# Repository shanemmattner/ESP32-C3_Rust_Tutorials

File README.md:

# ESP32-C3 Rust Tutorials

Various `embedded Rust tutorials` using the [ESP32-C3](https://www.espressif.com/en/products/socs/esp32-c3). We'll work towards making a `remote data logger` by first implementing peripherals we will need to build the larger project.

Each tutorial below has a `YouTube video` link where I will start with a blank project and implement a peripherals using the latest [esp-idf-hal](https://github.com/esp-rs/esp-idf-hal) version. 

## Repo organization

- [Tutorials](https://github.com/shanemmattner/ESP32-C3_Rust_Tutorials/tree/main/Tutorials): Source code for the [YouTube tutorials](https://youtube.com/playlist?list=PLkch9g9DEE0Lkm1LqcD7pZNDmXEczOo-a)
- [WIP](https://github.com/shanemmattner/ESP32-C3_Rust_Tutorials/tree/main/WIP): Half-baked crates that may have some useful code in the future
- [docs](https://github.com/shanemmattner/ESP32-C3_Rust_Tutorials/tree/main/docs): Various datasheets, books, and technical manuals
- [submodules](https://github.com/shanemmattner/ESP32-C3_Rust_Tutorials/tree/main/docs): All of the submodules for this repository.
   - <b>[referecnce projects](https://github.com/shanemmattner/ESP32-C3_Rust_Tutorials/tree/main/submodules/reference_projects)</b>: A huge collection of embedded Rust projects that I copy code from
- [Data-Logger-PCB](https://github.com/shanemmattner/ESP32-C3_Rust_Tutorials/tree/main/Data-Logger-PCB): KiCAD hardware designs for ESP32-C3 data logger PCB

## Part 0: Remote Data Logger MVP
[Minimum viable product](https://en.wikipedia.org/wiki/Minimum_viable_product) project where we'll implement all the peripherals and features we need for the data logger
- 4 ADC's
- 16 Digital I/O
- DHT11
- SD card logging
- UART CLI Shell

### Peripheral Tutorials
- [p0-output](https://youtu.be/vUSHaogHs1s): Make the "Hellow World" of embedded systems: a `Blinky application` to periodically turn an LED on and off
- [p1-input](https://youtu.be/2IY27b9TT2k): Add a button to turn the blinking logic on and off
- [p2-threads](https://youtu.be/ht5t39dEa4E): Move the button logic and LED logic to their own thread and pass messages between threads with [crossbeams channel](https://docs.rs/crossbeam/latest/crossbeam/channel/index.html)
- [p3-adc](https://youtu.be/07SVj6R_AhA): Read an [analog-to-digital converter channel](https://en.wikipedia.org/wiki/Analog-to-digital_converter) and print out the value
- [p4-dht11](tbd): Read a [DHT11](https://www.mouser.com/datasheet/2/758/DHT11-Technical-Data-Sheet-Translated-Version-1143054.pdf) for temperature and humidity data  
- [p5-i2c](https://youtu.be/NvEnHJPpavo): Configure and use a [SX1509 GPIO Expander](https://www.sparkfun.com/products/13601) through [I2C](https://learn.sparkfun.com/tutorials/i2c)
- [p6-spi](https://youtu.be/PUL8ehH6eUg): Write a string to a uSD card over SPI using [embedded-sdmmc](https://github.com/rust-embedded-community/embedded-sdmmc-rs) crate
- [p7-uart](https://youtu.be/-xEivxWe29M): Receiver characters from the UART and send them back when we detect a [carriage return](https://developer.mozilla.org/en-US/docs/Glossary/CRLF)

### Application Tutorials
- [p8-cli-shell](): Create a simple [CLI shell](https://interrupt.memfault.com/blog/firmware-shell) to interact with the ESP32-C3 over UART 
- [p9-adc-stream](): Configure ADC's to continuously read and make that data available to other parts of the application through a mutex
- [p10-log-values](): Log all the values read from the ADC's
- [p11-digital-stream](): Continuously read the SX1509 inputs and log to SD card

## Part 1: 
For the next part of the project we will add in features listed below:
- Debugging
- Logging
- FSM/HSM
- Wifi
- MQTT
- OTA
- Pub/sub
- Crash dumps & diagnostics

Other features I'd like to add but don't have a clear example for yet:
- DMA
- Timer usage

<details>
  <summary>Development environment setup</summary>
  
1. [Install Rust](https://esp-rs.github.io/book/installation/installation.html) and associated build tools
2. Start a project using the [esp-idf-template](https://github.com/esp-rs/esp-idf-template) from the private repo home `dir`. I chose all the default options
```
# STD Project
cargo generate https://github.com/esp-rs/esp-idf-template cargo
# NO-STD (Bare-metal) Project
cargo generate https://github.com/esp-rs/esp-template
```
3. Build the `Hello World` program by running `cargo build` in the new project dir. This will take a while to build the first time:
```
cd esp32-rust
cargo build
...
Finished dev [optimized + debuginfo] target(s) in 6m 40s
```
4. Flash the ESP32 with the build artifact:
```
espflash /dev/ttyACM0 target/riscv32imc-esp-espidf/debug/project
```
5. Connect to ESP32 and monitor
```
espmonitor /dev/ttyACM0
```
 </details>

<details>
  <summary>Misc</summary>
  
[Singletons in Embedded Rust](https://docs.rust-embedded.org/book/peripherals/singletons.html)

Pull in code for submodules with:
```
git submodule update --init --recursive
```
</details>

<details>
  <summary>Links</summary>

- [150+ ESP32 project](https://microcontrollerslab.com/esp32-tutorials-projects/)
- [Wokwi ESP32 Rust](https://wokwi.com/rust)
- [ESP32 Tutorials](https://embeddedexplorer.com/esp32/)
- [160+ ESP32 Projects, Tutorials, and Guides](https://randomnerdtutorials.com/projects-esp32/)

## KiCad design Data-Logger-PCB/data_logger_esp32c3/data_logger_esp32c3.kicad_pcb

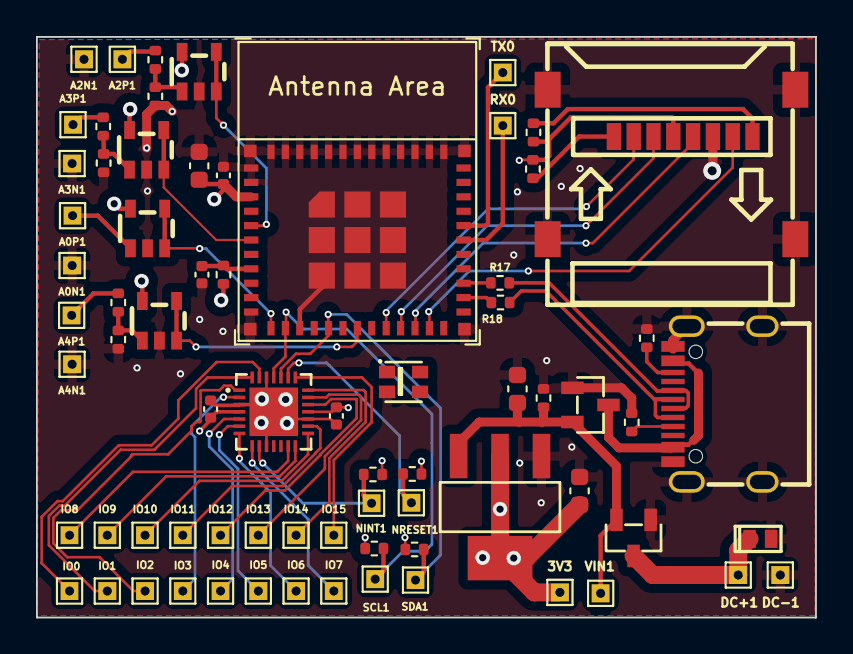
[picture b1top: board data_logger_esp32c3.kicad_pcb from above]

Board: 4 copper layers, 43.3 x 32.3 mm, 72 parts (0 on the bottom side), 47 nets.

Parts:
3V3: TestPoint; TestPoint_THTPad_1.0x1.0mm_Drill0.5mm
A0N1, A0P1, A2N1, A2P1, A3N1, A3P1, A4N1, A4P1: TestPoint; TestPoint_THTPad_1.0x1.0mm_Drill0.5mm
C1: 1uF; C_0402_1005Metric
C2, C4, C5: 10uF; C_0603_1608Metric
C3, C6, C7: 0.1uF; C_0402_1005Metric
D1: LTVS16H5.0T5G; DFN1610
DC+1: TestPoint; TestPoint_THTPad_1.0x1.0mm_Drill0.5mm
DC-1: TestPoint; TestPoint_THTPad_1.0x1.0mm_Drill0.5mm
IO0, IO1, IO2, IO3, IO4, IO5, IO6, IO7, IO8, IO9, IO10, IO11, IO12, IO13, IO14, IO15: TestPoint; TestPoint_THTPad_1.0x1.0mm_Drill0.5mm
NINT1: TestPoint; TestPoint_THTPad_1.0x1.0mm_Drill0.5mm
NRESET1: TestPoint; TestPoint_THTPad_1.0x1.0mm_Drill0.5mm
R1, R3, R4, R9, R14, R15: 10k; R_0402_1005Metric
R2, R7: 5.1k; R_0402_1005Metric
R5, R6, R13: 1k; R_0402_1005Metric
R8, R16: 4.7k; R_0402_1005Metric
R10: 1.6k; R_0402_1005Metric
R11: 3.92k; R_0402_1005Metric
R12: 7.5k; R_0402_1005Metric
R17, R18: 30.1; R_0402_1005Metric
RX0: TestPoint; TestPoint_THTPad_1.0x1.0mm_Drill0.5mm
SCL1: TestPoint; TestPoint_THTPad_1.0x1.0mm_Drill0.5mm
SD1: 472192001
SDA1: TestPoint; TestPoint_THTPad_1.0x1.0mm_Drill0.5mm
TX0: TestPoint; TestPoint_THTPad_1.0x1.0mm_Drill0.5mm
U1: ESP32-C3-MINI-1
U2: AZ1117IH-3.3TRG1; SOT-223-4
U3: WS2812B-2020
U4, U5, U6, U7: LM321MF
U9, U10: A03401A; SOT-23
U11: SX1509BIULTRT; QFN-28-EP(4x4)
USB-C1: USB-TYPE-C-018
VIN1: TestPoint; TestPoint_THTPad_1.0x1.0mm_Drill0.5mm

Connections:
+3V3: 3V3.1, C2.1, C3.1, C5.1, C6.1, C7.1, R1.2, R3.2, R4.1, R8.2, R14.2, R15.2, R16.2, SD1.4 (VDD), U1.3 (3V3), U2.2 (OUTPUT), U2.4 (VOUT), U3.4 (VDD), U4.5 (V+), U5.5 (V+), U6.5 (V+), U7.5 (V+), U11.4 (VCC1), U11.18 (VCC2)
+5V: U10.3 (D), USB-C1.A4 (VBUS), USB-C1.A9 (VBUS), USB-C1.B4 (VBUS), USB-C1.B9 (VBUS)
ADC1_CH0: U1.12 (GPIO0/ADC1_CH0/XTAL_32K_P), U4.3 (-), U4.4
ADC1_CH2: U1.5 (GPIO2/ADC1_CH2), U5.3 (-), U5.4
ADC1_CH3: U1.6 (GPIO3/ADC1_CH3), U6.3 (-), U6.4
ADC1_CH4: U1.18 (GPIO4/ADC1_CH4), U7.3 (-), U7.4
CS: SD1.2 (DAT3/CD), U1.20 (GPIO6)
D+: R17.1, U1.27 (GPIO19/USB_D+)
D-: R18.1, U1.26 (GPIO18/USB_D-)
DI: SD1.3 (CMD), U1.21 (GPIO7)
DO: SD1.7 (DAT0), U1.23 (GPIO9)
D_CONN+: R17.2, USB-C1.A6 (DP1), USB-C1.B6 (DP2)
D_CONN-: R18.2, USB-C1.A7 (DN1), USB-C1.B7 (DN2)
GND: A0N1.1, A2N1.1, A3N1.1, A4N1.1, C1.2, C2.2, C3.2, C4.2, C5.2, C6.2, C7.2, D1.2 (A), DC-1.1, R2.1, R5.2, R6.2, R7.1, R9.1, R13.2, SD1.6 (VSS), SD1.9 (SHIELD), SD1.10 (SHIELD), SD1.11 (SHIELD), SD1.12 (SHIELD), U1.1 (GND), U1.2 (GND), U1.11, U1.14, U1.36 (GND), U1.37 (GND), U1.38 (GND), U1.39 (GND), U1.40 (GND), U1.41 (GND), U1.42 (GND), U1.43 (GND), U1.44 (GND), U1.45 (GND), U1.46 (GND), U1.47 (GND), U1.48 (GND), U1.49 (GND), U1.50 (GND), U1.51 (GND), U1.52 (GND), U1.53 (GND), U2.1 (ADJ/GND), U3.2 (GND), U4.2 (V-), U5.2 (V-), U6.2 (V-), U7.2 (V-), U9.1 (G), U10.1 (G), U11.3 (GND), U11.10 (ADDR1), U11.17 (GND), U11.26 (ADDR0), U11.29 (PAD), USB-C1.0 (SH), USB-C1.1 (SH), USB-C1.2 (SH), USB-C1.3 (SH), USB-C1.A1 (GND), USB-C1.A12 (GND), USB-C1.B1 (GND), USB-C1.B12 (GND)
I2C_SCL: R8.1, SCL1.1, U1.13 (GPIO1/ADC1_CH1/XTAL_32K_N), U11.25 (SCL)
I2C_SDA: R16.1, SDA1.1, U1.16 (GPIO10), U11.24 (SDA)
NINT: NINT1.1, R15.1, U11.9 (NINT)
NRESET: NRESET1.1, R14.1, U11.23 (NRESET)
unnamed: A2P1.1, R10.1
unnamed: A3P1.1, R11.1
unnamed: A4P1.1, R12.1
unnamed: D1.1 (K), DC+1.1, U9.3 (D)
unnamed: R3.1, SD1.8 (DAT1)
unnamed: R1.1, SD1.1 (DAT2)
unnamed: C1.1, R4.2
unnamed: A0P1.1, U4.1 (+)
unnamed: R10.2, R13.1, U5.1 (+)
unnamed: R5.1, R11.2, U6.1 (+)
unnamed: R6.1, R12.2, U7.1 (+)
unnamed: C4.1, R9.2, U2.3 (INPUT), U9.2 (S), U10.2 (S), VIN1.1
unnamed: IO0.1, U11.27 (IO0)
unnamed: IO1.1, U11.28 (IO1)
unnamed: IO2.1, U11.1 (IO2)
unnamed: IO3.1, U11.2 (IO3)
unnamed: IO4.1, U11.5 (IO4)
unnamed: IO5.1, U11.6 (IO5)
unnamed: IO6.1, U11.7 (IO6)
unnamed: IO7.1, U11.8 (IO7)
unnamed: IO8.1, U11.13 (IO8)
unnamed: IO9.1, U11.14 (IO9)
unnamed: IO10.1, U11.15 (IO10)
unnamed: IO11.1, U11.16 (IO11)
unnamed: IO12.1, U11.19 (IO12)
unnamed: IO13.1, U11.20 (IO13)
unnamed: IO14.1, U11.21 (IO14)
unnamed: IO15.1, U11.22 (IO15)
SCLK: SD1.5 (CLK), U1.22 (GPIO8)

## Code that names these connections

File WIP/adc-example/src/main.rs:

use embedded_hal::adc::OneShot;
use esp_idf_hal::{
    adc::{self, Atten11dB, PoweredAdc},
    gpio,
    prelude::*,
};
use esp_idf_sys as _; // If using the `binstart` feature of `esp-idf-sys`, always keep this module imported
use std::{thread, time::Duration};
static BLINKY_STACK_SIZE: usize = 5000;

fn main() {
    // It is necessary to call this function once. Otherwise some patches to the runtime
    // implemented by esp-idf-sys might not link properly. See https://github.com/esp-rs/esp-idf-template/issues/71
    esp_idf_sys::link_patches();

    let peripherals = Peripherals::take().unwrap();

    let config = adc::config::Config::new().calibration(true);

    // let mut adc1_ch0 = peripherals.pins.gpio0.into_analog_atten_11db().unwrap();
    // let mut adc1_ch1 = peripherals.pins.gpio1.into_analog_atten_11db().unwrap();
    // let mut adc1_ch2 = peripherals.pins.gpio2.into_analog_atten_11db().unwrap();
    // let mut adc1_ch3 = peripherals.pins.gpio3.into_analog_atten_11db().unwrap();
    // let mut adc1_ch4 = peripherals.pins.gpio4.into_analog_atten_11db().unwrap();
    let mut adc2_ch0 = peripherals.pins.gpio5.into_analog_atten_11db().unwrap();

    // let mut adc1 = PoweredAdc::new(peripherals.adc1, config).unwrap();
    let mut adc2 = PoweredAdc::new(peripherals.adc2, config).unwrap();

    let _adc_thread = std::thread::Builder::new()
        .stack_size(BLINKY_STACK_SIZE)
        .spawn(move || loop {
            // let mut adc_reading = adc1.read(&mut adc1_ch0).unwrap();
            // println!("ADC1_0: {}", adc_reading);
            // adc_reading = adc1.read(&mut adc1_ch1).unwrap();
            // println!("ADC1_1: {}", adc_reading);
            // adc_reading = adc1.read(&mut adc1_ch2).unwrap();
            // println!("ADC1_2: {}", adc_reading);
            // adc_reading = adc1.read(&mut adc1_ch3).unwrap();
            // println!("ADC1_3: {}", adc_reading);
            // adc_reading = adc1.read(&mut adc1_ch4).unwrap();
            // println!("ADC1_4: {}", adc_reading);
            let mut adc_reading = adc2.read(&mut adc2_ch0).unwrap();
            println!("ADC2_0: {}", adc_reading);

            thread::sleep(Duration::from_millis(100));
        })
        .unwrap();
}

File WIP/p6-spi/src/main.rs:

use embedded_sdmmc::*;
use esp_idf_hal::{
    adc::{self, *},
    delay::FreeRtos,
    gpio::*,
    peripherals::Peripherals,
    prelude::*,
    spi::config::Duplex,
    spi::*,
};
use esp_idf_sys as _; // If using the `binstart` feature of `esp-idf-sys`, always keep this module imported
use esp_println::println;
use std::time::*;

const FILE_TO_CREATE: &'static str = "logs.txt";

pub struct SdMmcClock;

impl TimeSource for SdMmcClock {
    fn get_timestamp(&self) -> Timestamp {
        Timestamp {
            year_since_1970: 0,
            zero_indexed_month: 0,
            zero_indexed_day: 0,
            hours: 0,
            minutes: 0,
            seconds: 0,
        }
    }
}

fn main() {
    // It is necessary to call this function once. Otherwise some patches to the runtime
    // implemented by esp-idf-sys might not link properly. See https://github.com/esp-rs/esp-idf-template/issues/71
    esp_idf_sys::link_patches();

    println!("Starting 6-spi\nThis application writes ADC readings to a micro-SD card\n");

    let peripherals = Peripherals::take().unwrap();

    // ADC init
    let mut adc1 = AdcDriver::new(
        peripherals.adc1,
        &adc::config::Config::new().calibration(true),
    )
    .unwrap();
    let mut a1_ch0 =
        adc::AdcChannelDriver::<_, adc::Atten11dB<adc::ADC1>>::new(peripherals.pins.gpio0).unwrap();

    // SPI sd card init
    let driver = SpiDriver::new(
        peripherals.spi2,
        peripherals.pins.gpio8,       // SCK
        peripherals.pins.gpio7,       // PICO
        Some(peripherals.pins.gpio9), // POCI
        Dma::Disabled,
    )
    .unwrap();

    let mut spi_config = SpiConfig::new();
    spi_config.duplex = Duplex::Full;
    let _ = spi_config.baudrate(24.MHz().into());
    let spi = SpiDeviceDriver::new(driver, Option::<Gpio6>::None, &spi_config).unwrap();
    let sdmmc_cs = PinDriver::output(peripherals.pins.gpio6).unwrap();
    let mut sdmmc_spi = embedded_sdmmc::SdMmcSpi::new(spi, sdmmc_cs);

    // keep track of the time for logging
    let start_time = Instant::now();

    loop {
        match adc1.read(&mut a1_ch0) {
            Ok(adc_reading) => {
                match sdmmc_spi.acquire() {
                    Ok(block) => {
                        let mut controller = embedded_sdmmc::Controller::new(block, SdMmcClock);

                        let mut volume =
                            controller.get_volume(embedded_sdmmc::VolumeIdx(0)).unwrap();

                        let root_dir = controller.open_root_dir(&volume).unwrap();

                        let mut f = controller
                            .open_file_in_dir(
                                &mut volume,
                                &root_dir,
                                FILE_TO_CREATE,
                                Mode::ReadWriteCreateOrAppend,
                            )
                            .unwrap();

                        f.seek_from_end(0).unwrap();
                        // Create log string
                        let mut log_string: String = start_time.elapsed().as_millis().to_string();
                        log_string.push_str(&",A1_CH0,".to_string());
                        log_string.push_str(&(adc_reading as u32).to_string());
                        log_string.push('\n');
                        // Write the string to the SD card
                        let _bytes_written = controller
                            .write(&mut volume, &mut f, &log_string.as_bytes()[..])
                            .unwrap();
                        println!("String written: {log_string}");

                        controller.close_file(&volume, f).unwrap();
                    }
                    Err(e) => println!("Error acquire SPI bus {:?}", e),
                };
            }
            Err(e) => println!("err reading A1_CH0: {e}\n"),
        }

        FreeRtos::delay_ms(500);
    }
}

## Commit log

2023-01-14 working first blinky
2023-01-16 Added outline to README
2023-01-16 Added thread blinky
2023-01-16 add fsm blinky
2023-01-18 add wifi project
2023-01-18 working blinky with wifi
2023-01-19 wifi test
2023-01-19 added project
2023-01-24 improve blinky thread
2023-01-24 improved ch03 fsm
2023-01-24 improve wifi example
2023-01-24 moved fsm to its own file
2023-01-24 adding more chapters
2023-01-24 edit readme
2023-01-25 add heirarchical state machine example
2023-01-25 adding multi-state machine example
2023-01-26 add submodules
2023-01-26 Rearrange chapters
2023-01-26 Added multi-thread example
2023-01-26 refactor logic
2023-01-26 refactor blinky
2023-01-27 add example with crossbeam
2023-01-29 added no-std example
2023-02-01 adding async example and adc
2023-02-11 update crate versions"
2023-02-11 upgrade crates to latest
2023-02-11 deleted unused project
2023-02-11 modifying submodule
2023-02-11 adding more projects to submodules
2023-02-11 adding reference examples
2023-02-11 more submodules
2023-02-11 remove commented out code
2023-02-11 non-macro working
2023-02-11 updated fsm example to latest esp-idf drivers
2023-02-11 add readme, change name
2023-02-11 hsm working without blinking led
2023-02-11 working hsm with latest esp-idf libraries
2023-02-11 ch05 working with latest esp-idf drivers
2023-02-12 updated cross-beams example
2023-02-12 convert more examples to latest esp-idf
2023-02-13 removing examples
2023-02-14 Adding adc example
2023-02-14 led pwm working
2023-02-14 connected adc and led pwm
2023-02-15 Made gpio passing generic
2023-02-15 refactor fsm to use generic output
2023-02-15 remove type print
2023-02-15 converted HSM to generic IO
2023-02-15 convert example to use generic io
2023-02-15 LED pwm driver example working
2023-02-16 remove WIP example
2023-02-18 interrupt is working kinda
2023-02-18 interrupt kinda working...
2023-02-19 adding comments and refactoring
2023-02-19 corrected LED fsm
2023-02-19 refactor ch03
2023-02-19 add comments and change pin direction
2023-02-20 readme update
2023-02-20 broke out tasks into a seperate file
2023-02-20 passing enum around
2023-02-20 adding chapter 7
2023-02-20 wifi connecting
2023-02-20 compiles
2023-02-20 code compiles, untested
2023-02-20 remove unused imports
2023-02-20 fix bug
2023-02-20 refactor
2023-02-20 remove unused code
2023-02-20 change name of file
2023-02-20 refactor to use esp_println
2023-02-21 add blinky gif, refactor
2023-02-21 resize gif
2023-02-21 refactor names
2023-02-21 created button example, moved WIP projects to different folder
2023-02-21 add readme about pull down resistor for chapter 3
2023-02-21 added pull-down config
2023-02-21 add example with 2 threads
2023-02-21 changed README
2023-02-21 adding submodule
2023-02-22 working example
2023-02-22 led example working as expected
2023-02-22 example working as expected
2023-02-22 added submodule
2023-02-22 somewhat working neopixel example
2023-02-22 change to 1sec interval
2023-02-22 moved neopixel code to a different file
2023-02-22 adding files for future projects
2023-02-23 changed name of example
2023-02-23 compiling mqtt example
2023-02-23 connecting to wifi
2023-02-23 expanding wifi setup
2023-02-23 printing out wifi info
2023-02-23 adding more
2023-02-23 moved functions to different files
2023-02-23 sending mqtt event...somewhere"
2023-02-24 clean up warnings
2023-02-24 ignoring file
2023-02-24 added error handling for mqtt reception
2023-02-24 trying mqtt stuff
2023-02-24 kinda working?
2023-02-24 moved wifi/mqtt to WIP
2023-02-27 sd card working
2023-02-27 working sd card example
2023-02-27 talking to sx1509
2023-02-27 add pull-ups
2023-02-27 working
2023-02-27 moved projects to different folder
2023-02-27 adc example working
2023-02-27 refactor and add neopixel
2023-02-27 refactor and add protections
2023-02-27 refactor and add example
2023-02-27 move files around and rename
2023-02-27 changed names, added spi sd card example
2023-02-27 writing adc values to SD card
2023-02-27 add submodule for sd-card
2023-02-27 adding readmes for chapters
2023-02-27 change names of folders
2023-02-27 change readme
2023-02-28 refactor and add gif of neopixel example
2023-02-28 fix bugs
2023-02-28 remove gifs
2023-02-28 refactor sd card example to remove error checking
2023-03-01 uart kinda working
2023-03-01 printing out numbers
2023-03-02 refactor, adding to p7
2023-03-02 printing out stuff
2023-03-02 echo working
2023-03-02 getting there
2023-03-02 solved bug of starving main thread
2023-03-02 added delete character recognition
2023-03-02 make uart write its own function
2023-03-02 splitting input command
2023-03-02 finding hashmap entry
2023-03-02 p7 kinda working
2023-03-02 simplify sd card example
2023-03-02 simplify uart example
2023-03-02 remove unused
2023-03-03 Add hardware, reorganize repo
2023-03-03 refactor folder organization
2023-03-03 try different libraries
2023-03-03 starting to make thread
2023-03-03 working!
2023-03-03 working DHT11 tutorial
2023-03-03 move neopixel to WIP
2023-03-03 update readme to use dht11 example instead of neopixel
2023-03-03 formatting data properly
2023-03-09 Implement CLI using UART peripheral
2023-03-09 simplify repo structure
2023-03-09 remove WIP crates we dont need anymore
2023-03-10 change name of readme file
2023-03-11 initializing adc
2023-03-11 almost working
2023-03-11 kinda working
2023-03-12 all channels working with struct
2023-03-12 thread working
2023-03-13 printing values through uart between threads
2023-03-13 printng values
2023-03-15 printing uart readings
2023-12-31 Update deps to fix error
2023-12-31 Update build command to use `espflash flash` instead of just `espflash`
2023-12-31 Rename crate to `output` for `p0-output`
2024-01-05 Update deps and fix errors for adc tutorial
2024-01-10 Update deps to fix error (#5)
2024-01-10 Update build command to use `espflash flash` instead of just `espflash` (#6)
2024-01-10 Rename crate to `output` for `p0-output` (#7)
2024-01-10 Fix adc tutorial (#9)
    * Update build command to use `espflash flash` instead of just `espflash`
    * Update deps and fix errors for adc tutorial
